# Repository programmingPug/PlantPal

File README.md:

<br/>
<div align="center">

<h3 align="center">PlantPal</h3>
<p align="center">
Because knowing when to water your plants is hard

</p>
</div>

## About The Project

I love having plants around but I often forget to water them or how much to water them. So I initially started this project to just check if soil was dry and have a small piezo buzzer go off when a plant needed water. Well things escalated as I wanted to add features and now I'm at the point where it's a multi-system product with multiple moving parts. 

Where the project is now

At this point the project consists of:
- Probe nodes that record soil moisture data
- Reporter node that collects and sends the probe data to an API
- An API that serves to both the reporter node and a front-end client
- Front-end client that provides a web interface for viewing the collected plant moisture data.

Where the project is going

The end goal is to have the probe nodes collect soil moisture, soil temperature, relative humidity, air temperature and light spectrum values. With all this information I'm hoping to be able to optimism plant health and maybe even help figure out resource distribution for farming... but that's years down the road.
### Built With

This project is built on the following technologies:

- [NPM](https://www.npmjs.com/)
- [Node](https://nodejs.org/en)
- [Node](https://www.docker.com/)
- [Angular](https://angular.dev/)
- [.Net](https://dotnet.microsoft.com/en-us/download)
- [XAIO ESP32-C6](https://wiki.seeedstudio.com/xiao_esp32c6_getting_started/)
- [Eagle](https://www.autodesk.com/products/eagle/overview?term=1-YEAR&tab=subscription)
- [Arduino](https://www.arduino.cc/)

## Project Structures:

- plant-browser: Front-end client.
- SoilMoistureAPI: Backend API.
- Eagle: PCB project for soil nodes.
- batteryValidationTest: Arduino project for testing batteries.
- soilReporterNode: Arduino project for probe notes to report and forward data to API.
- soilProbeNode: Arduino project for gathering plant information.

## Requirement (Client and API)

- Node: v22.12.0
- NPM: v10.9.0
- Docker: v27.4.0

## Requirement (Hardware)
- Arduino IDE: v10
 - WiFiManager
 - Additional Boards: (https://espressif.github.io/arduino-esp32/package_esp32_index.json)
- XAIO ESP32C6
- Soil Sensor 2.0
- Miscellaneous electrical components

## Installing for Local Development:

### API:
You will need to modify a few things int he API project for local development.

1) program.cs
```js
options.ListenAnyIP(80) --> options.ListenAnyIP(8000)
```

2) appsettings.json
```js
"DefaultConnection": "Data Source=app/data/SoilMoisture.db" --> "DefaultConnection": "Data Source=SoilMoisture.db"
```

Then just click "http" to run the API.

## Install client dependencies:
From the client folder

Install dependencies
```sh
npm install
```

Run the Client:
```sh
ng s
```

## Building Images:
Building images for runtime distrobution

### API image:

Build docker image
```sh
docker build --no-cache -t plantpal-api:latest .
```

Tag image
```sh
docker image tag plantpal-api 192.168.1.193:5000/plantpal-api
```

Push to registry
```sh
docker push 192.168.1.193:5000/plantpal-api
```

### Client image:
Building images for runtime distrobution

Build docker image
```sh
docker build -t plantpal-client:latest .
```

Tag image
```sh
docker image tag plantpal-client 192.168.1.193:5000/plantpal-client
```

Push to registry
```sh
docker push 192.168.1.193:5000/plantpal-client
```

## Running Docker Images:

### Create Docker Network
Create new docker network for the containers to communicate
```sh
docker network create plantpal_network
```

### Run API Image

```sh
docker run -d --name plantpal_api --network plantpal_network -p 8000:80 plantpal_api:latest
```

### Run Client Image
```sh
docker run -d --name plantpal_client --network plantpal_network -p 3000:80 plantpal_client:latest
```

### Docker Compose:
optionally You can also use docker compose with the file at the root

```sh
docker-compose up -d --build
```

## Roadmap

- [X] Functional API
- [X] Functional Client
- [X] Functional reporter node
- [ ] Functional prob node
- [X] Unraid integration
- [X] Initial PCB design 
## Contributing

Currently this is closed to contributing till V1 is functional.
## License

Distributed under the MIT License. See [MIT License](https://opensource.org/licenses/MIT) for more information.
## Contact

Christopher Koch - ckoch@lazypug.net

Project Link: https://github.com/programmingPug/plantpal

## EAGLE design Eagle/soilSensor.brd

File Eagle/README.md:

<br/>
<div align="center">

<h3 align="center">PlantPal</h3>
<p align="center">
Because knowing when to water your plants is hard
</p>
</div>

## PCB features

### Eagle Cad
- Autodesk Eagle CAD
- More information to come...

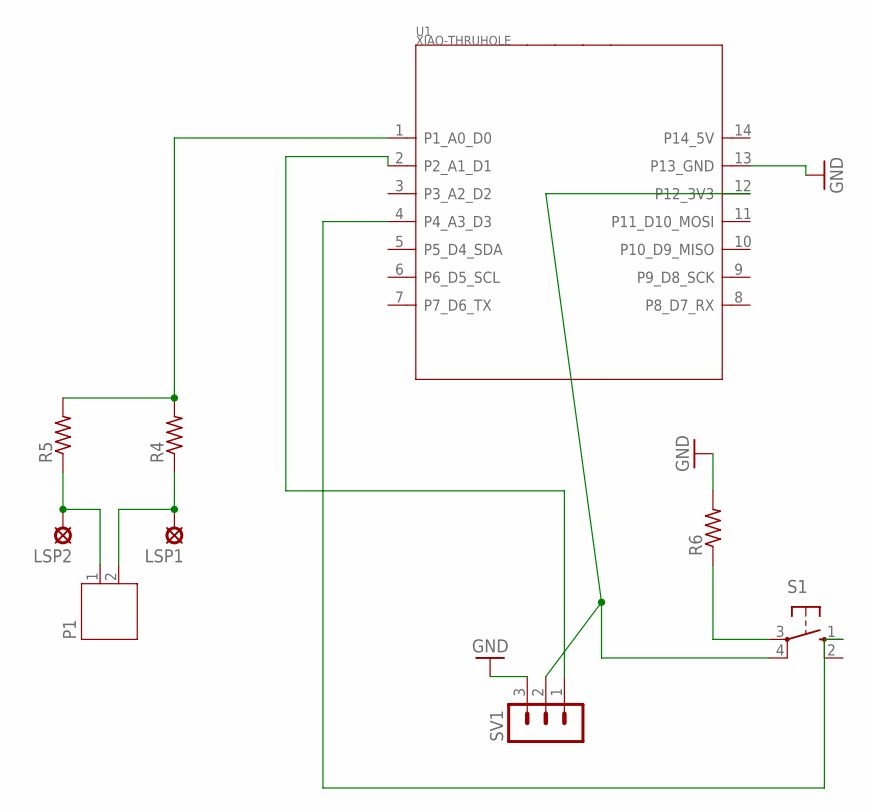
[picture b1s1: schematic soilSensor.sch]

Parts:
LSP1, LSP2: LSP10
P1: JST-PH2
R4, R5, R6: R-US_0204/7; 0204/7
S1: 10-XX; B3F-10XX
SV1: MA03-1
U1: XIAO-THRUHOLE; XIAO-GENERIC-THRUHOLE-MODULE14P-2.54-21X17.8MM

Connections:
GND: R6.2, SV1.3, U1.13 (P13_GND)
unnamed: R4.2, R5.2, U1.1 (P1_A0_D0)
unnamed: LSP2.MP, P1.1, R5.1
unnamed: LSP1.MP, P1.2, R4.1
unnamed: S1.1 (S), U1.4 (P4_A3_D3)
unnamed: SV1.1, U1.2 (P2_A1_D1)
unnamed: R6.1, S1.3
unnamed: S1.4 (P1), SV1.2, U1.12 (P12_3V3)

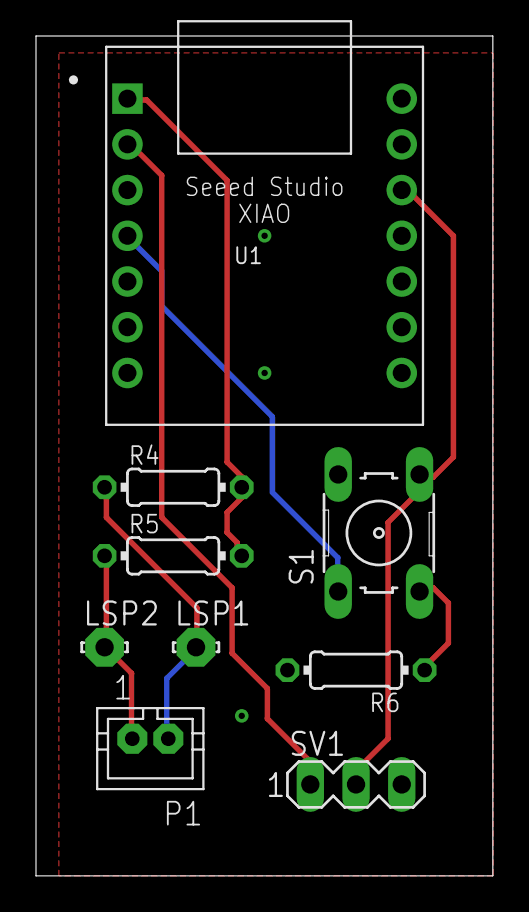
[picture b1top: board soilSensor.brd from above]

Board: 2 copper layers, 25.4 x 46.7 mm, 9 parts (0 on the bottom side), 8 nets.

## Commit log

2023-03-03 initial commit - api
2023-05-07 test
2025-01-04 API updates for functional code
2025-01-04 Updates to API and added arduino code for the XIAO-ESP32C6
2025-01-04 Remove old client and add new
2025-01-14 Major rewrite
2025-01-14 Reporter node Updates
2025-01-14 update API for more simple approach.
2025-01-15 Add new code for battery validation, updated probe node code added base read me
2025-01-15 Refine readme
2025-01-15 fix image
2025-01-15 got it this time
2025-01-16 Runtime and readme updates
2025-01-16 Reporter node readme
2025-01-16 Updated Readme's
2025-01-16 Readme updates
2025-01-17 Update client for api changes and nickname attr
